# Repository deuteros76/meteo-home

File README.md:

# meteo-home
MeteoHome was born as a weather station project using a NodeMCU ESP8266 devboard with DHT22 and BMP180 sensors. Now, the concept has changed and the board (currently a Wemos D1 Lite) and the source are being redesigned to allow the use of different type of sensors. One of the main features of MeteoHome is the configuration using a captive web portal and the use of MQTT to send the information to a server. Additionally, it has been designed to be connected to a machine running Home Assistant. In this case, this software could be used to show the current status of the sensors and display graphs.

## Features
- configuration of WiFi network and MQTT through a web portal 
- Deep sleep mode included for being powered by battery 
- Temperature, humidity, air pressure and air quality measurements depending on the sensors plugged to the board ( currently DHT22, BMP180, SGP30 or AHT20)
- Support for analog sensors (moisture, proximity) with configurable value mapping
- Enhanced captive portal with improved UI and grouped settings panels
- Possibility of being used with Home Assistant

### Supported Sensors
MeteoHome supports multiple sensor types that can be used simultaneously:

- DHT22: Temperature (°C) and humidity (%) measurements
- BMP180: Temperature (°C) and atmospheric pressure (Pa)
- SGP30: Air quality monitoring with CO2 (ppm) and VOC (ppb) measurements
- AHT20: High-precision temperature (°C) and humidity (%) readings
- Analog Sensors: Configurable for moisture (%) or proximity (mm) measurements through A0 pin

### LED Indicators
The board includes three status LEDs. These LEDs provide visual feedback during boot sequence and runtime operation:

During boot:

- All LEDs flash once during initial power-up
- Green LED indicates successful boot and connection

During operation with SGP30 air quality monitoring:

- Green LED: Indicates good air quality (CO2 < 600 ppm)
- Yellow LED: Indicates moderate air quality (CO2 600-800 ppm)
- Red LED: Indicates poor air quality (CO2 > 800 ppm)

## Future
The idea is to continue the development of both hardware and software. Currently the MCU is a Wemos D1 Lite but the plan is to extend the possibilities including an ESP32 or a Raspberry Pi Pico, At the same time, the software will accept more sensors and will be adapted to the new hardware.

- Integration of light sensor
- ~~Integration of ATH20 sensor~~
- Adoption of a new MCU (ESP32 or Raspberry Pi Pico)
- Hardware redesign for the new MCU
- Development of software for the new board 

## Requirements
- PlatformIO IDE (used to build, test and check quality of code)
- Additional libraries: WiFiManager, Arduino Json, PubSubClient, DHT, Adafruit BMP085 and Adafruit AHTX0 (see platformio.ini)
- A computer running MQTT
- [Optional] A computer running Home Assistant

## Building the software

To build the software PlatformIO is needed. There are two options, the first one is to use the IDE and the second, covered here, is to use the pio command:

```shell
pio run --environment d1_mini_lite
```

## Hardware

The hardware has been designed in Kicad. All the source files are available under the Kicad directory of this repository.

### Hardware components
- Wemos D1 Mini Lite (the board is designed to use this microcontroller)
- One or more sensors (DHT22, BMP180, SGP-30)
- Analog sensors (moisture, proximity sensors connected to A0 pin)
- Wires, tools...

Below the current BOM is shown. There are no sensors included, as the idea is to plug any of the supported and are not considered part of the hardware design:

|#  |Reference|Qty|Value                     |LibPart                                                     |Footprint|
|---|---------|---|--------------------------|------------------------------------------------------------|----|
|1  |A1       |1  |Analog Sensor            |Connector:Conn_01x03_Socket                                 |Connector_PinSocket_2.54mm:PinSocket_1x03_P2.54mm_Vertical|
|2  |D1       |1  |Red                      |meteo-home-rescue:LED-meteo-home-rescue-co2-detector-rescue |LED_THT:LED_D3.0mm|
|3  |D2       |1  |Yellow                   |meteo-home-rescue:LED-meteo-home-rescue-co2-detector-rescue |LED_THT:LED_D3.0mm|
|4  |D3       |1  |Green                    |meteo-home-rescue:LED-meteo-home-rescue-co2-detector-rescue |LED_THT:LED_D3.0mm|
|5  |DHT22    |1  |DHT22_Temperature_Humidity|meteo-home-rescue:DHT22_Temperature_Humidity-sensors-meteo-home-rescue-co2-detector-rescue|Sensors:DHT22_Temperature_Humidity|
|6  |I2C1     |1  |I2C 1                    |Connector:Conn_01x04_Socket                                |Connector_PinSocket_2.54mm:PinSocket_1x04_P2.54mm_Vertical|
|7  |I2C2     |1  |I2C 2                    |Connector:Conn_01x04_Socket                                |Connector_PinSocket_2.54mm:PinSocket_1x04_P2.54mm_Vertical|
|8  |I2C3     |1  |I2C 3                    |Connector:Conn_01x04_Socket                                |Connector_PinSocket_1.00mm:PinSocket_1x04_P1.00mm_Vertical|
|9  |I2C4     |1  |I2C 4                    |Connector:Conn_01x04_Socket                                |Connector_PinSocket_1.00mm:PinSocket_1x04_P1.00mm_Vertical|
|10 |J1       |1  |S 4                      |Connector:Conn_01x04_Socket                                |Connector_PinSocket_2.54mm:PinSocket_1x04_P2.54mm_Vertical|
|11 |MCU1     |1  |WeMos_D1_mini            |meteo-home-rescue:WeMos_D1_mini-wemos_mini-meteo-home-rescue-co2-detector-rescue|Module:WEMOS_D1_mini_light|
|12 |PWR1     |1  |Power connector          |Connector:Conn_01x02_Socket                                |Connector_Molex:Molex_SL_171971-0002_1x02_P2.54mm_Vertical|
|13 |R1, R2   |2  |160                      |meteo-home-rescue:R-meteo-home-rescue-co2-detector-rescue  |Resistor_THT:R_Axial_DIN0204_L3.6mm_D1.6mm_P5.08mm_Horizontal|
|14 |R3       |1  |90                       |meteo-home-rescue:R-meteo-home-rescue-co2-detector-rescue  |Resistor_THT:R_Axial_DIN0204_L3.6mm_D1.6mm_P5.08mm_Horizontal|
|15 |R4       |1  |10K                      |meteo-home-rescue:R-meteo-home-rescue-co2-detector-rescue  |Resistor_THT:R_Axial_DIN0204_L3.6mm_D1.6mm_P5.08mm_Horizontal|
|16 |Tx1      |1  |Rx                       |Connector:Conn_01x02_Socket                                |Connector_PinSocket_2.54mm:PinSocket_1x02_P2.54mm_Vertical|

## Configuring a meteo-home device
After uploading the sketch and the first execution the device will run as an Access Point. Check the available networks for you computer and connect with "meteo-home". After that, point your browser to http://192.168.4.1 and the captive portal will be displayed. 

> **Note:** on some Android phones, the system's captive-portal-login popup can show a stale or incomplete cached version of the page (e.g. missing the "Network settings"/"MQTT Server settings"/"Device parameters" fields on the "Configure WiFi" page). If that happens, open a regular browser (Chrome, Firefox, etc.) and navigate to http://192.168.4.1 manually instead of using the auto-launched popup.

Choose the first option ("Configure WiFi") and select your home WiFi network from the list of detected APs and introduce its password. 

Now you have to configure your network settings. Below, the fields related to your MQTT server should be introduced. Then, in the "Device parameters" section, it is required to introduce a word identifying your device (you can use a name or the location where it will be installed). This value will be used to create the topics where the data will be sent through MQTT. 

The device supports analog sensors connected to the A0 pin. Through the captive portal, you can:

- Enable/disable analog sensor reading
- Select sensor class (moisture or proximity)
- Configure value mapping between raw analog readings (0-1024) to percentage (0-100%)
- Set minimum and maximum thresholds for the mapping function

The improved captive portal now features:

- Grouped settings panels for better organization
- Dynamic show/hide of configuration options
- Real-time value preview using range sliders
- Enhanced visual styling and layout

## Remote reconfiguration

Once configured, a MeteoHome device can be reconfigured without physical access by
publishing an MQTT command. Only device/sensor parameters can be changed (not network or
MQTT credentials, which still require deleting `config.json` and going through the portal
again).

Each device has a secret 32-character token (`config_token`), generated automatically. On a
new device it is shown on the captive portal page, next to the device name. On a device
updated from a firmware version prior to this feature, the token is generated on the first
boot after the update and printed once over Serial (9600 baud) — check it before it's lost,
or delete `config.json` to go through the portal again and see it there.

To reconfigure, publish a JSON with `retain=true` to `meteohome/<device>/config/set`,
including the token and only the fields you want to change:

```shell
mosquitto_pub -h <broker> -t 'meteohome/attic/config/set' -r \
  -m '{"token":"<config_token>","sleep_minutes":10,"device_name":"attic"}'
```

Accepted fields: `device_name`, `use_sleep_mode`, `sleep_minutes` (1-60),
`use_analog_sensor`, `sensor_class`, `use_arduino_map_function`, `analog_min_value` and
`analog_max_value` (0-1024, with `analog_min_value < analog_max_value`).

The device responds on `meteohome/<device>/config/result` (not retained):

- `{"status":"applied","fields":[...]}` — change applied; the device restarts.
- `{"status":"error","reason":"invalid_token"}` — token missing or incorrect.
- `{"status":"error","reason":"invalid_payload"}` — malformed JSON.
- `{"status":"error","reason":"invalid_field:<name>"}` — a field is out of range or of the
  wrong type; no change is applied (transactional validation).

After processing the command (whether successful or not), the device clears the retained
message on `config/set` so it isn't reprocessed on the next reconnection.

In addition, on every connection to the broker the device publishes its current
configuration (without the token) as retained on `meteohome/<device>/config/state`:

```json
{
  "device_name": "attic",
  "use_sleep_mode": true,
  "sleep_minutes": 15,
  "use_analog_sensor": false,
  "sensor_class": "moisture",
  "use_arduino_map_function": true,
  "analog_min_value": 0,
  "analog_max_value": 1024
}
```

This topic makes it possible to build a form (for example, in Home Assistant) that
auto-fills with the device's real values before sending a change.

### Remote reconfiguration page

`tools/remote-config.html` is a self-contained page (HTML + JS, no backend or external
dependencies) that reads a device's state and applies changes without hand-crafting JSON.
Open it directly as a local file in your browser (double-click or `file://`).

**Prerequisite (one-time, on your broker):** enable a WebSocket listener. In Mosquitto, add
to the configuration:

```
listener 9001
protocol websockets
```

and restart the service. Without this, the page won't be able to connect.

**Usage:**
1. Open `tools/remote-config.html` in your browser.
2. Under "Broker connection", enter your broker's host and WebSocket port (the `9001` from
   the example above), and the MQTT username/password if your broker requires them. Click
   "Connect".
3. Under "Device", enter the device's `device_name` and its token, and click "Read current
   state" — the form will fill in with the device's real values.
4. Edit whichever fields you want to change and click "Apply changes". The device will
   apply the change (or return an error) and the result will appear in the "Result"
   section.

Connection details and each device's token are saved in the browser's `localStorage` where
you open the page, so you don't have to re-enter them every time — the same level of trust
you already assume by storing those same credentials elsewhere (e.g. Home Assistant). If you
expose the broker's WebSocket listener beyond your local network, do so at your own security
discretion; this page adds no extra protection on top of the existing token.

## Using MeteoHome with Home Assistant
A MeteoHome device publishes the data it collects to a MQTT broker. The topics used follow the specifications made by Home Assistant project and it is possible to use this software to store and use MeteoHome produced data. When a MeteoHome board is connected to a power source, it sends Home Assisant autodiscovery messages making it available through the MQTT integration.

If Home Assistant is not your preferred option, any other software that includes a MQTT broker could be used to obtain the data. To get the data, the software should be configured to subscribe to the appropriate topics. As an example the following topics are availabe if a DHT22 and SGP-30 sensors are plugged to a board configured with "attic" as topic prefix:

| Sensor  | Topic  |   |   |   |
|---|---|---|---|---|
| DHT22  | attic/DHT22/temperature  | DHT22 temperature value  |   |   |
| DHT22  | attic/DHT22/humidity  | DHT22 humidity value  |   |   |
| DHT22  | attic/DHT22/heatindex  | DHT22 heat index value  |   |   |
| SGP30  | attic/SGP30/co2  | SGP30 CO2 ppp  |   |   |
| SGP30  | attic/SGP30/voc  | SGP30 air quality |   |   |
| ESP8266  | attic/ESP/vcc  | ESP8266/microcontroller voltage   |   |   |
| Analog  | attic/moisture/value | Moisture sensor percentage |
| Analog  | attic/proximity/value | Proximity sensor value |
| AHT20 | attic/AHT20/temperature | AHT20 temperature value |
| AHT20 | attic/AHT20/humidity | AHT20 humidity value |

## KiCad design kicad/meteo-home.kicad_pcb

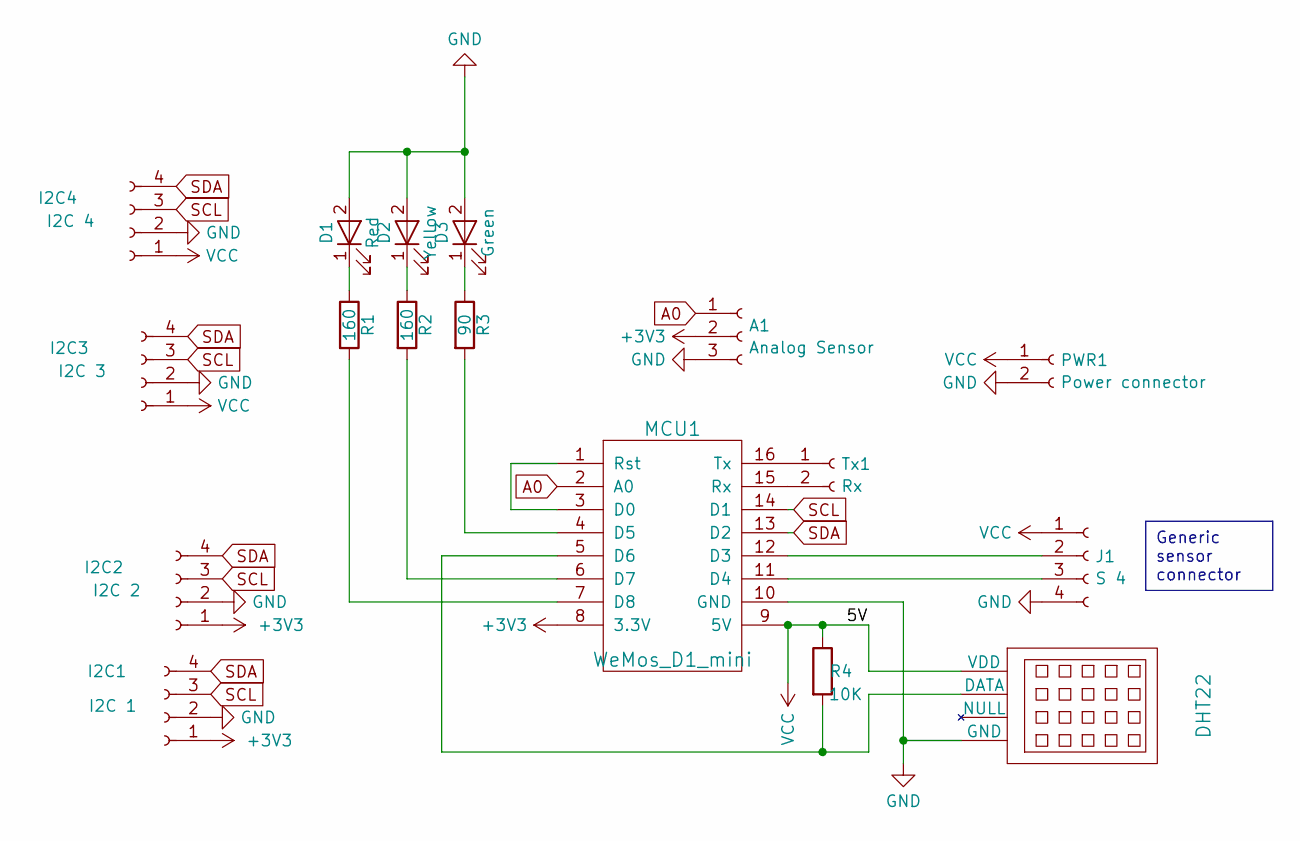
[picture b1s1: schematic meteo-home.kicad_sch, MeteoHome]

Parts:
A1: Analog Sensor; PinSocket_1x03_P2.54mm_Vertical
D1: Red; LED_D3.0mm
D2: Yellow; LED_D3.0mm
D3: Green; LED_D3.0mm
DHT22: DHT22_Temperature_Humidity
I2C1: I2C 1; PinSocket_1x04_P2.54mm_Vertical
I2C2: I2C 2; PinSocket_1x04_P2.54mm_Vertical
I2C3: I2C 3; PinSocket_1x04_P1.00mm_Vertical
I2C4: I2C 4; PinSocket_1x04_P1.00mm_Vertical
J1: S 4; PinSocket_1x04_P2.54mm_Vertical
MCU1: WeMos_D1_mini; WEMOS_D1_mini_light
PWR1: Power connector; Molex_SL_171971-0002_1x02_P2.54mm_Vertical
R1, R2: 160; R_Axial_DIN0204_L3.6mm_D1.6mm_P5.08mm_Horizontal
R3: 90; R_Axial_DIN0204_L3.6mm_D1.6mm_P5.08mm_Horizontal
R4: 10K; R_Axial_DIN0204_L3.6mm_D1.6mm_P5.08mm_Horizontal
Tx1: Rx; PinSocket_1x02_P2.54mm_Vertical

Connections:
+3V3: A1.2, I2C1.1, I2C2.1, MCU1.8 (3.3V)
A0: A1.1, MCU1.2 (A0)
GND: A1.3, D1.2 (A), D2.2 (A), D3.2 (A), DHT22.4 (GND), I2C1.2, I2C2.2, I2C3.2, I2C4.2, J1.4, MCU1.10 (GND), PWR1.2
unnamed: D1.1 (K), R1.1
unnamed: D2.1 (K), R2.1
unnamed: D3.1 (K), R3.1
unnamed: DHT22.2 (DATA), MCU1.5 (D6), R4.2
unnamed: J1.2, MCU1.12 (D3)
unnamed: J1.3, MCU1.11 (D4)
unnamed: MCU1.1 (Rst), MCU1.3 (D0)
unnamed: MCU1.4 (D5), R3.2
unnamed: MCU1.6 (D7), R2.2
unnamed: MCU1.7 (D8), R1.2
unnamed: MCU1.15 (Rx), Tx1.2
unnamed: MCU1.16 (Tx), Tx1.1
SCL: I2C1.3, I2C2.3, I2C3.3, I2C4.3, MCU1.14 (D1)
SDA: I2C1.4, I2C2.4, I2C3.4, I2C4.4, MCU1.13 (D2)
VCC: DHT22.1 (VDD), I2C3.1, I2C4.1, J1.1, MCU1.9 (5V), PWR1.1, R4.1

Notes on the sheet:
Generic sensor connector

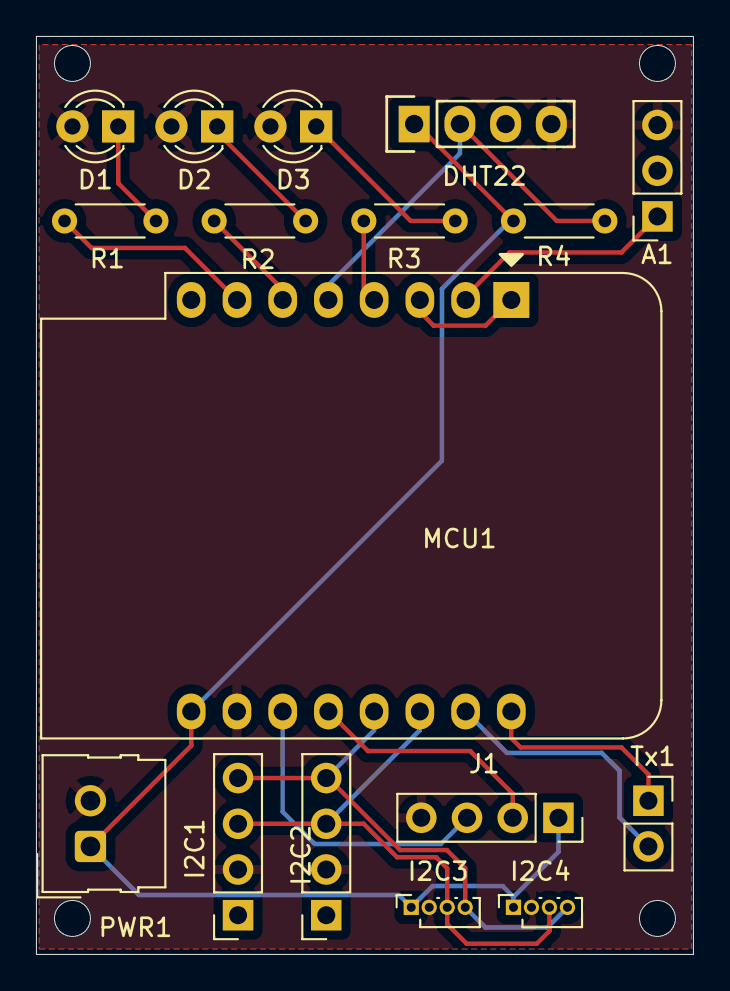
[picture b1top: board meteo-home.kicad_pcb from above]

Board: 2 copper layers, 36.5 x 51.0 mm, 17 parts (0 on the bottom side), 18 nets.

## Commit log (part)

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2016-11-21 Initial commit. Work in progress
2016-11-24 Added more parameters
2016-11-26 First working version
2016-11-27 Basic information
2016-11-27 Hardware components
2016-11-27 Some pics added
2016-11-27 Pictures added
2016-11-27 Readme revised
2016-11-28 Adding more images
2016-11-28 Links to images
2016-11-28 Fixed linked image
2016-11-29 Bread board picture
2016-11-29 More pictures
2016-11-29 Fixing typos
2016-12-06 Home assistant configuration added
2016-12-06 Home Assistant explained
2016-12-06 File deleted
2016-12-06 Link to configuration.yaml
2016-12-08 code refactoring
2016-12-08 Refactoring of variables
2016-12-08 pin changed
2016-12-16 breadboad picture
2017-05-08 Better timeout management
2017-07-12 Server IP using a string caused an error
2017-07-12 Use the mqtt port from the settings file
2017-07-12 Missing include caused an error
2017-07-12 Default port changed
2017-08-09 Sever string and pull up/down config removed.
2017-08-10 DCHP removed. Now requires manual configuration but this makes the device more efficent
2017-08-10 Bugfix: exception fixed when the BMP180 was not connected
2020-10-12 Trying to fix a wrong configuration adter setting up all the required values
2020-10-12 First complete design of the PCB
2020-10-12 Gerber files
2022-09-02 Better connection process control
2022-09-02 refactoring: now using a newer (which incompatible with the previous version) ArduinoJSON library
2022-09-02 fix: avoid exceptions when sensors are not working and not giving values
2022-09-02 fix: correct hostname
2022-09-02 fix: hostname is correctly assigned. Format is Meteo-home_MACADDRESS
2022-09-02 fix: board updated to the last one used in co2-detector
2022-09-02 fix: allow deep sleep conecting RST and D0
2022-09-05 feat: new configuration paramete to use the sleep mode or not
2022-09-06 feat: discovery message for Homeassistant
2022-09-07 fix: device class removed as it is not parameterized
2022-09-07 fix: topic name corrected
2022-09-18 feat: better usage of LEDs during the setup function
2022-12-10 feat: BMP180 is detected if is connected to the SGP30 header. This requires to to change the wiring between SCL and SDA. Currently only prints the information trough the serial monitor
2023-08-10 feat: discovery parameters to identify better all sensors in Home Assistant and make them available to statistics
2023-08-12 fix: better management of messages and correction of some bpm180 parameters
2023-08-12 feat: send only discovery messages in the first boot when using deep sleep
2023-08-15 feat: turn on the LEDs during the first boot when using deep sleep mode
2023-08-15 feat: adding labels to the sensors holes
2023-08-16 feat: simplified configuration form. MQTT topics are generated from the device name parameter.
2023-08-16 feat: deep sleep mode form input changed to checkbox type
2023-08-19 refactor: separete classes for the different sensors conected
2023-08-19 refactor: including a class for SGP30
2023-08-19 refactor: adapted to platform.io
2023-08-21 feat: SGP30 support added. First working version
2023-08-21 fix: fixes on BMP180 sensor
2023-08-22 refactor: sensor topics are not stored in the json configuration file anymore. The properties and functions related to them have been moved to the appropriate sensor class
2023-08-22 fix: do not send discovery messages for DHT if it is not available
2023-08-23 refactor: better format of output messages and reduced number of printings to Serial
2023-09-01 feat: new class for managing the ESP board. Currently is similar to sensor classes but it is expected to ibclude differente methods and properties in the future
2023-09-01 doc: build badge added
2023-09-01 doc: CICD project name changed
2023-09-04 refactor: using an array of sensort objects to simplify and reduce the code. Sensor objects are directly using the mqtt client object
2023-09-05 refactor: normalizing output messages for DHT and BMP sensors
2023-09-05 refactor: discovery messages are sent by the corresponding sensor object
2023-09-17 refactor: refactoring main loop and setup code. Hpp files moved to include dir. Preparing a testing environment
2023-09-17 feat: firs tests added
2023-09-17 fix: available function blocked value reading after the first error (nan values) was detected
2023-09-29 refactor: using standard vector to store pointers to the different sensor objects
2023-09-30 fix: missing manager include file recovered
2023-09-30 refactor: test changed to use std::vector for storing object pointers (as in the project source code)
2023-09-30 refactor: new LED class to manage all red, green and yellow, the LEDs
2023-10-01 refactor: SGP30 LEDs dependency injection
2023-10-01 refactor: reducing the number of prints
2023-10-03 refactor: manager object is a meteosensor member
2023-10-20 refactor: sensor discovery messages and values publication are moved to the board class. Now a board has a vector of sensors
2023-11-03 refactor: pubsubclient object is now a member of meteoboard
2023-11-03 fix: base line is read and saved again
2023-11-06 fix: option for including the header files directory
2023-11-10 fix: tests adapted to the refactored classes
2023-11-11 refactor: SPIFFS replaced by LittleFS
2023-11-11 feat: file structure created to separete different tests depending on their classes
2023-11-26 feat: cppcheck included to chech the quality of code.
2023-12-02 doc: Readme file updated
2023-12-02 README.md corrections
2023-12-09 fix: refill before sending to factory
2023-12-09 feat: reset after configuration is saved. This avoids WiFiManager to connect using DHCP (this only happened fater saving the config data)
2024-08-21 feat: aht20 humidity and temperatures sensor is now supported
2024-08-25 Fix: corrected values for the discovery message of the AHT20 humidity sensor
2024-08-25 feat: added a message in case of error in message (end) publishing
2024-08-25 feat: new components added (RX/TX)
2024-09-08 Feat: i2c connectors pins and disposition changed
2024-09-09 Fix: connectors relocation
2024-09-24 Feat: last chenges. Sent to factory
2024-10-05 feat: analaog sensor reading. Testing with a moisture sensor
2024-10-06 feat: adding more parameters (including range html inputs for the first time) to the form. The configuration information is now used in the main.cpp file
2024-10-06 fix: when first booting after pluging in the porwe cable, analogRead was reading VCC
2024-10-10 feat: configuration form improvementes. Dinamically showing and hidding elements. More parameters available: analog sensor can use or not the Arduino map function
2024-10-10 refactor: Manager class refactor to use right types
2024-10-12 feat: sensor class is configured base on the deviceclass parameter requested in the web form ;
2024-10-14 feat: nullptr detection
2024-10-17 feat: better layout and style for the html form
2024-10-17 fix: exception throw removed
2024-10-21 fix: wrong topic name corrected
2024-10-22 fix: wrong topic path corrected
2024-10-24 doc: more information about sensors and LEDs
2024-10-29 docs: updated version of the Readme file replacing outdated images
2024-10-30 fix: static IP connection is woking through WifiManager
2024-11-18 doc: jekyll web site created
2024-11-24 feat: first version of the web site working
2024-11-28 doc: improving the website adding pagination and styling the list. This required the mdification of the pytonh script to add css tags when producing the markdown files
2024-11-29 feat: python script to download and convert posts from my joomla blog site
2024-11-30 feat: create thumbnail images
2024-11-30 feat: use thumbnail in home sidebar
2024-12-01 feat: use the publishing date from the source article
2024-12-01 fix: post image display
2026-02-18 fix: wrong temperature character
2026-03-27 feat: add OTA (Over-The-Air) update support
    - Add ArduinoOTA integration with hostname "meteo-home"
    - Add 30-second OTA wait window at startup to allow firmware uploads
    - Add OTA event handlers for progress, errors, and completion logging
    - Add new PlatformIO environment 'd1_mini_lite_ota' for OTA uploads
    - Handle OTA in main loop for updates outside the startup window
    Amp-Thread-ID: https://ampcode.com/threads/T-019d30ba-f078-76fe-abf6-7dc0b423f4f2
2026-03-27 feat: improve MQTT reliability and Home Assistant integration
    - Subscribe to homeassistant/status topic and resend discovery messages
    when Home Assistant restarts (via MQTT callback)
    - Move autodiscover() call outside first_boot_done check so discovery
    runs on every boot cycle
    - Add expires_after (300s) to sensor discovery messages
    - Simplify sendDiscoveryMessage using client->print() and keep
2026-03-28 feat: add MQTT availability topic and improve non-sleep loop
    - Configure MQTT Last Will and Testament (LWT) with "offline" status
    and publish "online" on connect via "meteohome/status" topic
    - Replace discovery exp_aft with availability object referencing
    the new availability topic
    - In non-sleep mode, replace blocking delay with an active loop that
    processes MQTT messages and OTA updates
2026-03-28 Update Python version to 3.15 in workflow
2026-03-28 Update Python version in GitHub Actions workflow
